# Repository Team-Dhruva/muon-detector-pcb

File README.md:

Note: I'm using KiCad 10.0. Please maintain a proper record of things in this repository.

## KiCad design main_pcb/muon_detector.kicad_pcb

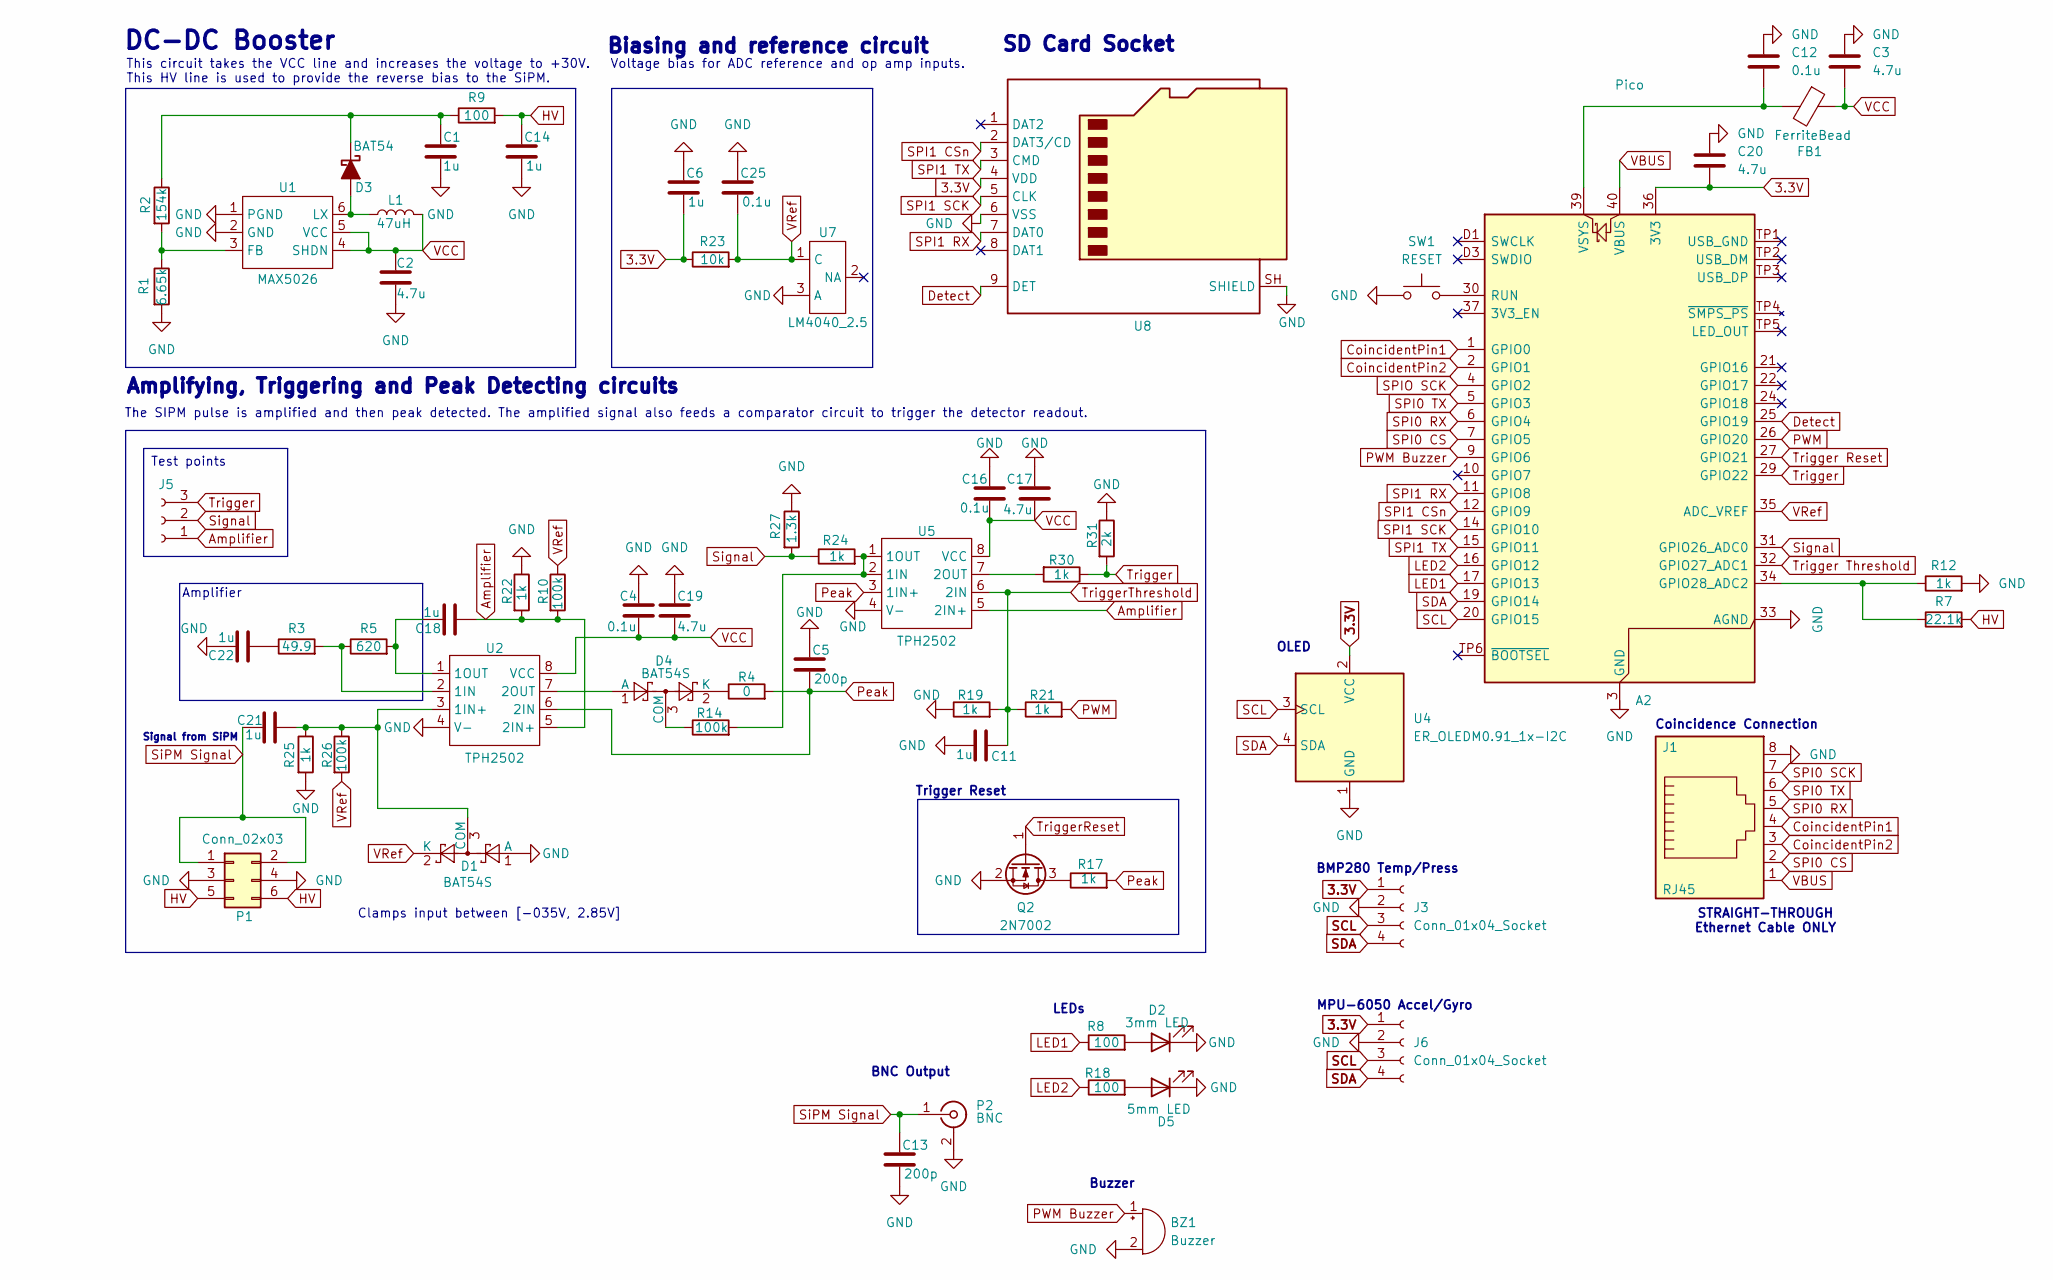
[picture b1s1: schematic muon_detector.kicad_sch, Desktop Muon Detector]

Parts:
A2: Pico; RaspberryPi_Pico_SMD_HandSolder
BZ1: Buzzer; MagneticBuzzer_ProSignal_ABT-410-RC
C1, C6, C11, C14, C18, C21, C22: 1u; C_0805_2012Metric_Pad1.18x1.45mm_HandSolder
C2, C3, C17, C19, C20: 4.7u; C_0805_2012Metric_Pad1.18x1.45mm_HandSolder
C4, C12, C16, C25: 0.1u; C_0805_2012Metric_Pad1.18x1.45mm_HandSolder
C5, C13: 200p; C_0805_2012Metric_Pad1.18x1.45mm_HandSolder
D1, D4: BAT54S; SOT-23
D2: 3mm LED; LED_D3.0mm
D3: BAT54; D_SOD-323F
D5: 5mm LED; LED_D5.0mm
FB1: FerriteBead; WE-CBF_0805_W4.0
J1: RJ45; RJ45_Amphenol_RJHSE5380
J3, J6: Conn_01x04_Socket; PinSocket_1x04_P2.54mm_Vertical
J5: Conn_01x03_Socket; PinSocket_1x03_P1.27mm_Vertical
L1: 47uH; L_0805_2012Metric_Pad1.05x1.20mm_HandSolder
P1: Conn_02x03; PinHeader_2x03_P2.54mm_Vertical
P2: BNC; CONN_73137-5003_MOL
Q2: 2N7002; SOT-23
R1: 6.65k; R_0603_1608Metric_Pad0.98x0.95mm_HandSolder
R2: 154k; R_0603_1608Metric_Pad0.98x0.95mm_HandSolder
R3: 49.9; R_0805_2012Metric_Pad1.20x1.40mm_HandSolder
R4: 0; R_0805_2012Metric_Pad1.20x1.40mm_HandSolder
R5: 620; R_0805_2012Metric_Pad1.20x1.40mm_HandSolder
R7: 22.1k; R_0805_2012Metric_Pad1.20x1.40mm_HandSolder
R8, R9, R18: 100; R_0805_2012Metric_Pad1.20x1.40mm_HandSolder
R10, R14, R26: 100k; R_0805_2012Metric_Pad1.20x1.40mm_HandSolder
R12, R17, R19, R21, R22, R24, R25, R30: 1k; R_0805_2012Metric_Pad1.20x1.40mm_HandSolder
R23: 10k; R_0805_2012Metric_Pad1.20x1.40mm_HandSolder
R27: 1.3k; R_0805_2012Metric_Pad1.20x1.40mm_HandSolder
R31: 2k; R_0805_2012Metric_Pad1.20x1.40mm_HandSolder
SW1: RESET; Reset_Button_PTS645VH83-2_LFS
U1: MAX5026; TSOT-23-6_HandSoldering
U2, U5: TPH2502; SOP-8_3.76x4.96mm_P1.27mm
U4: ER_OLEDM0.91_1x-I2C; OLED_0.96inch_custom
U7: LM4040_2.5; TSOT-23
U8: Micro_SD_Card_Det1; microSD_HC_Hirose_DM3D-SF

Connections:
3.3V: A2.36 (3V3), C6.2, C20.2, J3.1, J6.1, R23.1, U4.2 (VCC), U8.4 (VDD)
Amplifier: C18.2, J5.1, R10.2, R22.2, U2.5 (2IN+), U5.5 (2IN+)
CoincidentPin1: A2.1 (GPIO0), J1.4
CoincidentPin2: A2.2 (GPIO1), J1.3
Detect: A2.25 (GPIO19), U8.9 (DET)
GND: A2.33 (AGND), BZ1.2 (-), C1.2, C2.2, C3.1, C4.1, C5.1, C6.1, C11.1, C12.1, C13.2, C14.2, C16.1, C17.1, C19.1, C20.1, C22.1, C25.1, D1.1 (A), D2.1 (K), D5.1 (K), J1.8, J3.2, J6.2, P1.3, P1.4, P2.2 (Ext), Q2.2 (S), R1.2, R12.2, R19.1, R22.1, R25.2, R27.1, R31.1, SW1.1, U1.1 (PGND), U1.2 (GND), U2.4 (V-), U4.1 (GND), U5.4 (V-), U7.3 (A), U8.6 (VSS), U8.SH (SHIELD)
HV: C14.1, P1.5, P1.6, R7.2, R9.2
LED1: A2.17 (GPIO13), R8.1
LED2: A2.16 (GPIO12), R18.1
unnamed: A2.3 (GND), A2.8 (GND), A2.13 (GND), A2.18 (GND), A2.23 (GND), A2.28 (GND), A2.38 (GND), A2.D2 (GND)
unnamed: A2.34 (GPIO28_ADC2), R7.1, R12.1
unnamed: A2.30 (RUN), SW1.2
unnamed: A2.39 (VSYS), C12.2, FB1.2
unnamed: C22.2, R3.1
unnamed: C21.2, D1.3 (COM), R25.1, R26.1, U2.3 (1IN+)
unnamed: D2.2 (A), R8.2
unnamed: D3.2 (A), L1.1, U1.6 (LX)
unnamed: C1.1, D3.1 (K), R2.1, R9.1
unnamed: D4.1 (A), U2.7 (2OUT)
unnamed: D4.3 (COM), R14.1
unnamed: D4.2 (K), R4.1
unnamed: D5.2 (A), R18.2
unnamed: Q2.3 (D), R17.1
unnamed: R1.1, R2.2, U1.3 (FB)
unnamed: R3.2, R5.1, U2.2 (1IN)
unnamed: C18.1, R5.2, U2.1 (1OUT)
unnamed: R14.2, R24.2, U5.1 (1OUT), U5.2 (1IN)
unnamed: R30.2, U5.7 (2OUT)
PWM: A2.26 (GPIO20), R21.2
PWM Buzzer: A2.9 (GPIO6), BZ1.1 (+)
Peak: C5.2, R4.2, R17.2, U2.6 (2IN), U5.3 (1IN+)
SCL: A2.20 (GPIO15), J3.3, J6.3, U4.3 (SCL)
SDA: A2.19 (GPIO14), J3.4, J6.4, U4.4 (SDA)
SPI0 CS: A2.7 (GPIO5), J1.2
SPI0 RX: A2.6 (GPIO4), J1.5
SPI0 SCK: J1.7
SPI0 TX: A2.5 (GPIO3), J1.6
SPI1 CSn: A2.12 (GPIO9), U8.2 (DAT3/CD)
SPI1 RX: A2.11 (GPIO8), U8.7 (DAT0)
SPI1 SCK: A2.14 (GPIO10), U8.5 (CLK)
SPI1 TX: A2.15 (GPIO11), U8.3 (CMD)
SPIO SCK: A2.4 (GPIO2)
SiPM Signal: C13.1, C21.1, P1.1, P1.2, P2.1 (In)
Signal: A2.31 (GPIO26_ADC0), J5.2, R24.1, R27.2
Trigger: A2.29 (GPIO22), J5.3, R30.1, R31.2
Trigger Reset: A2.27 (GPIO21)
Trigger Threshold: A2.32 (GPIO27_ADC1)
TriggerReset: Q2.1 (G)
TriggerThreshold: C11.2, R19.2, R21.1, U5.6 (2IN)
VBUS: A2.40 (VBUS), J1.1
VCC: C2.1, C3.2, C4.2, C16.2, C17.2, C19.2, FB1.1, L1.2, U1.4 (SHDN), U1.5 (VCC), U2.8 (VCC), U5.8 (VCC)
VRef: A2.35 (ADC_VREF), C25.2, D1.2 (K), R10.1, R23.2, R26.2, U7.1 (C)

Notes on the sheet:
Trigger Reset
LEDs
STRAIGHT-THROUGH Ethernet Cable ONLY
Voltage bias for ADC reference and op amp inputs.
SD Card Socket
MPU-6050 Accel/Gyro
Buzzer
Clamps input between [-035V, 2.85V]
Amplifying, Triggering and Peak Detecting circuits
BNC Output
This circuit takes the VCC line and increases the voltage to +30V. This HV line is used to provide the reverse bias to the SiPM.
DC-DC Booster
Test points
Biasing and reference circuit
Signal from SiPM
OLED
BMP280 Temp/Press
Coincidence Connection
The SIPM pulse is amplified and then peak detected. The amplified signal also feeds a comparator circuit to trigger the detector readout.
Amplifier

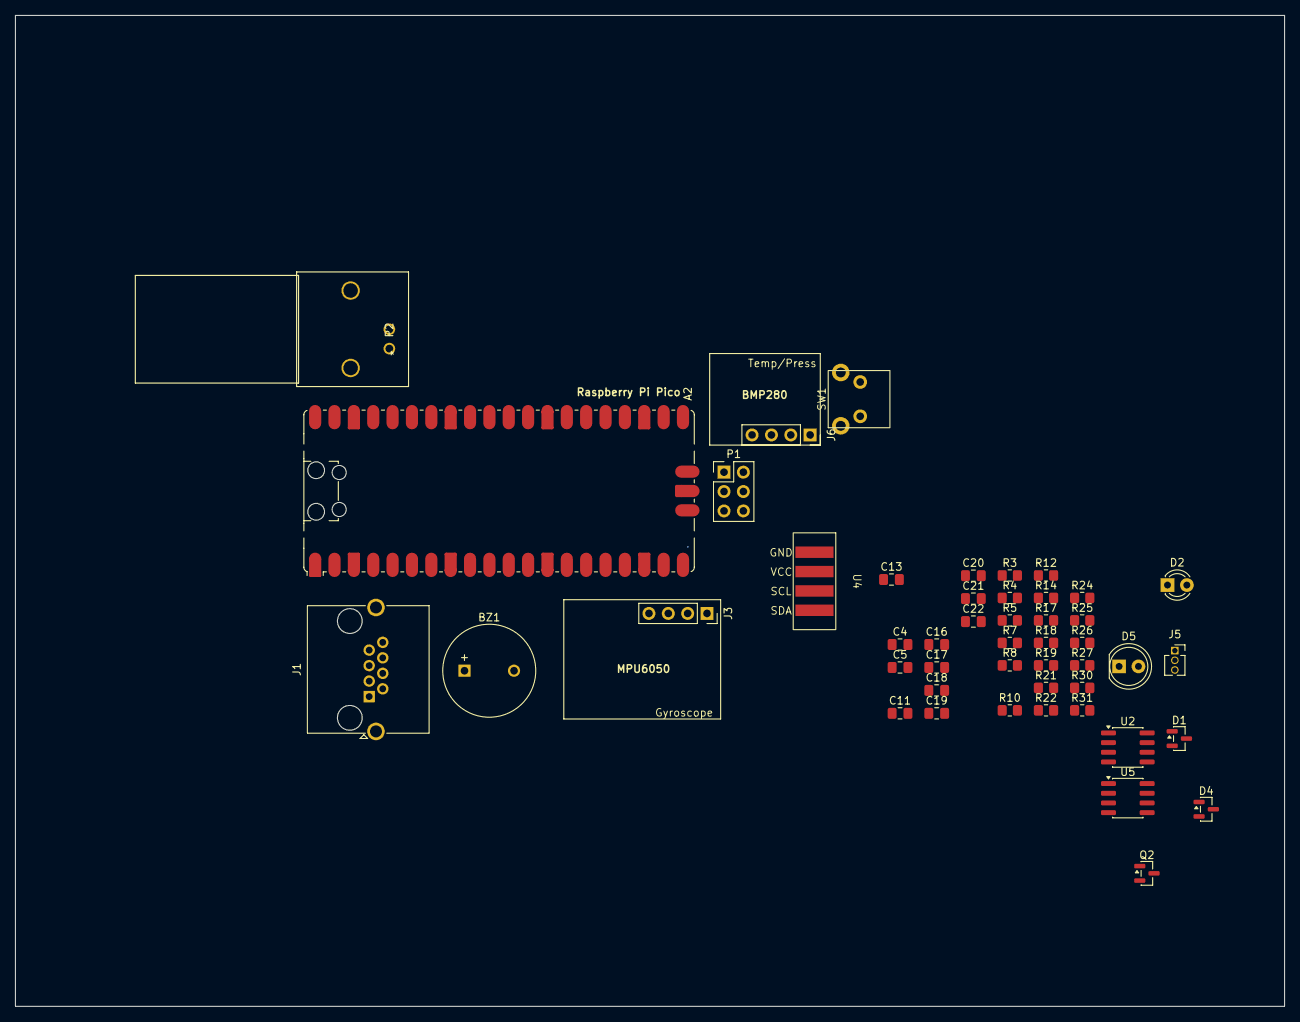
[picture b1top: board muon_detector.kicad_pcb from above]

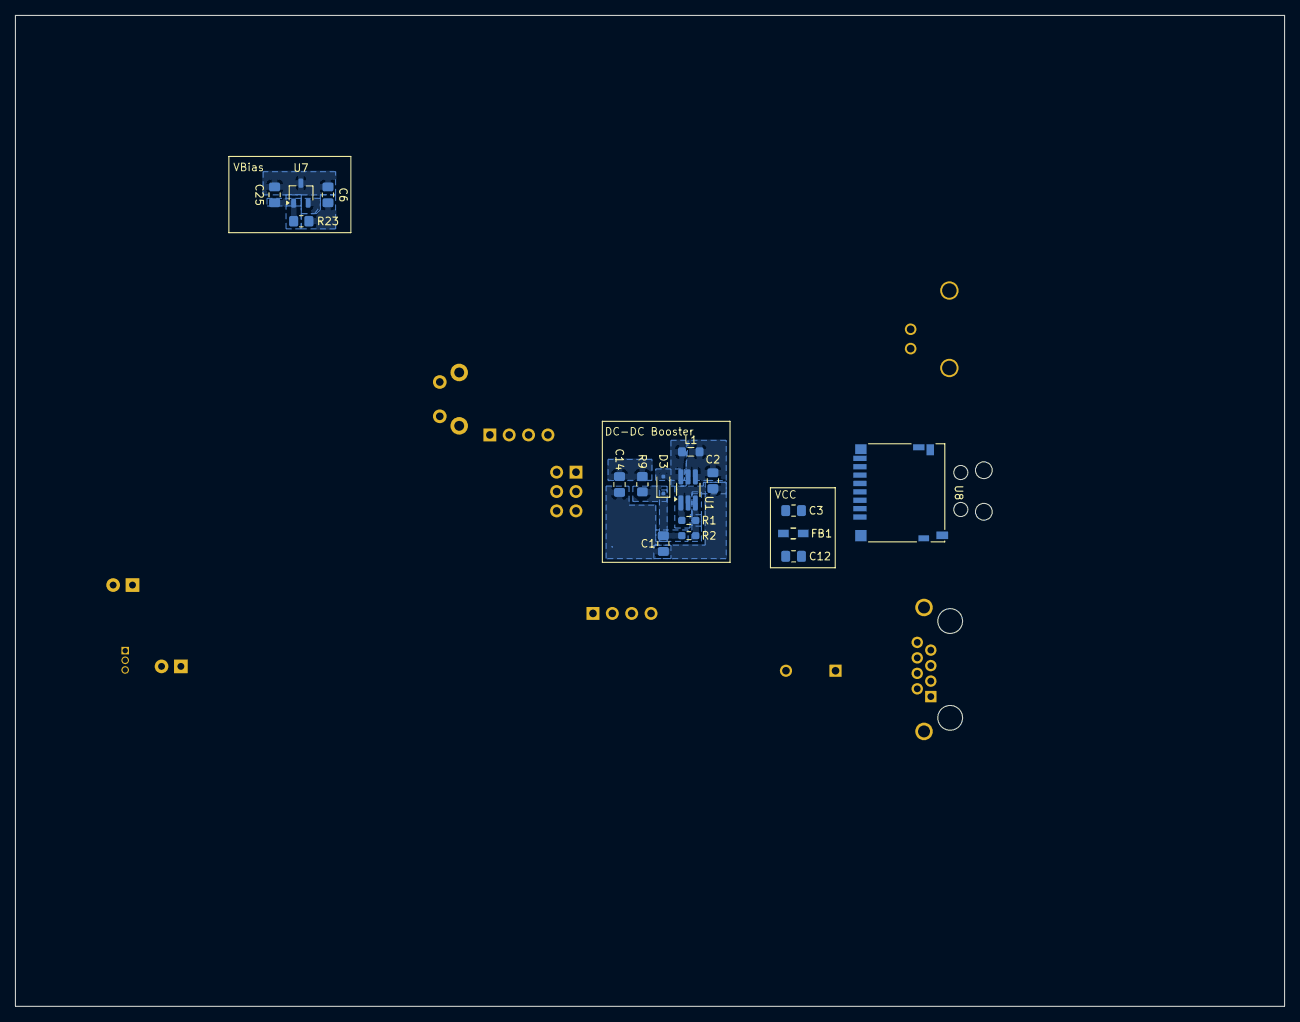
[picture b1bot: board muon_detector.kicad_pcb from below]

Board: 2 copper layers, 166.5 x 130.0 mm, 64 parts (17 on the bottom side), 47 nets.
